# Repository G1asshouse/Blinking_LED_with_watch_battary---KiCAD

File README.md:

# Blinking_LED_with_watch_battary

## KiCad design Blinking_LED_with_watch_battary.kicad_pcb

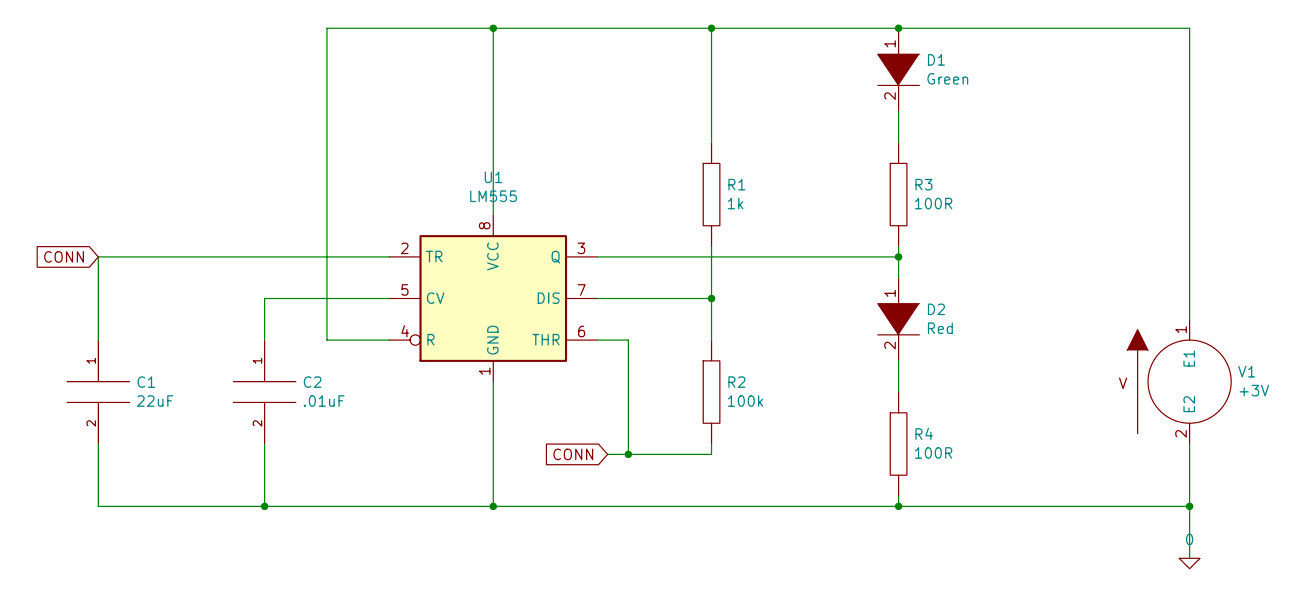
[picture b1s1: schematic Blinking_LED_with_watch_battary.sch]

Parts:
C1: 22uF; C_0805_2012Metric_Pad1.15x1.40mm_HandSolder; Manufacturer PN CL21A226KOQNNNE
C2: .01uF; C_0805_2012Metric_Pad1.15x1.40mm_HandSolder; Manufacturer PN CL21B103KAANNNC
D1: Green; LED_0805_2012Metric_Pad1.15x1.40mm_HandSolder; Manufacturer PN LG R971-KN-1
D2: Red; LED_0805_2012Metric_Pad1.15x1.40mm_HandSolder; Manufacturer PN LH R974-LP-1
R1: 1k; R_0805_2012Metric_Pad1.15x1.40mm_HandSolder; Manufacturer PN RC2012J104CS
R2: 100k; R_0805_2012Metric_Pad1.15x1.40mm_HandSolder; Manufacturer PN RC2012J102CS
R3, R4: 100R; R_0805_2012Metric_Pad1.15x1.40mm_HandSolder; Manufacturer PN RC2012J101CS
U1: LM555; SOIC-8_3.9x4.9mm_P1.27mm; Manufacturer PN LM555CMX/NOPB
V1: +3V; BatteryHolder_Keystone_3001_1x12mm; Manufacturer PN 3001

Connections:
0: C1.2, C2.2, R4.2, U1.1 (GND), V1.2 (E2)
CONN: C1.1, R2.2, U1.2 (TR), U1.6 (THR)
unnamed: C2.1, U1.5 (CV)
unnamed: D1.1 (K), R1.1, U1.4 (R), U1.8 (VCC), V1.1 (E1)
unnamed: D1.2 (A), R3.1
unnamed: D2.1 (K), R3.2, U1.3 (Q)
unnamed: D2.2 (A), R4.1
unnamed: R1.2, R2.1, U1.7 (DIS)

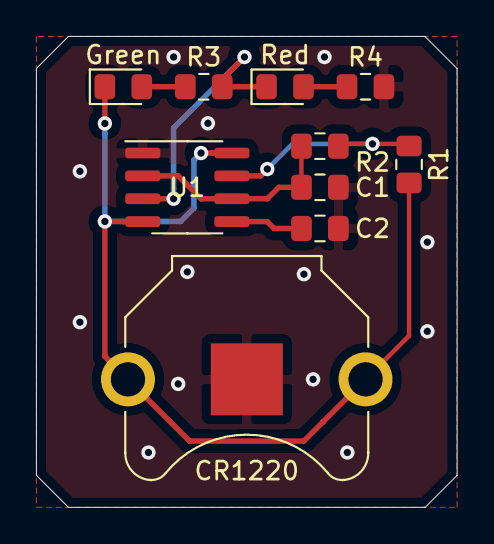
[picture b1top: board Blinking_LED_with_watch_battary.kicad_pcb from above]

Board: 2 copper layers, 23.4 x 26.2 mm, 10 parts (0 on the bottom side), 8 nets.
